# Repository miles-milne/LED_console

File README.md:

WORK IN PROGRESS

Current project of making 2048 using hardware

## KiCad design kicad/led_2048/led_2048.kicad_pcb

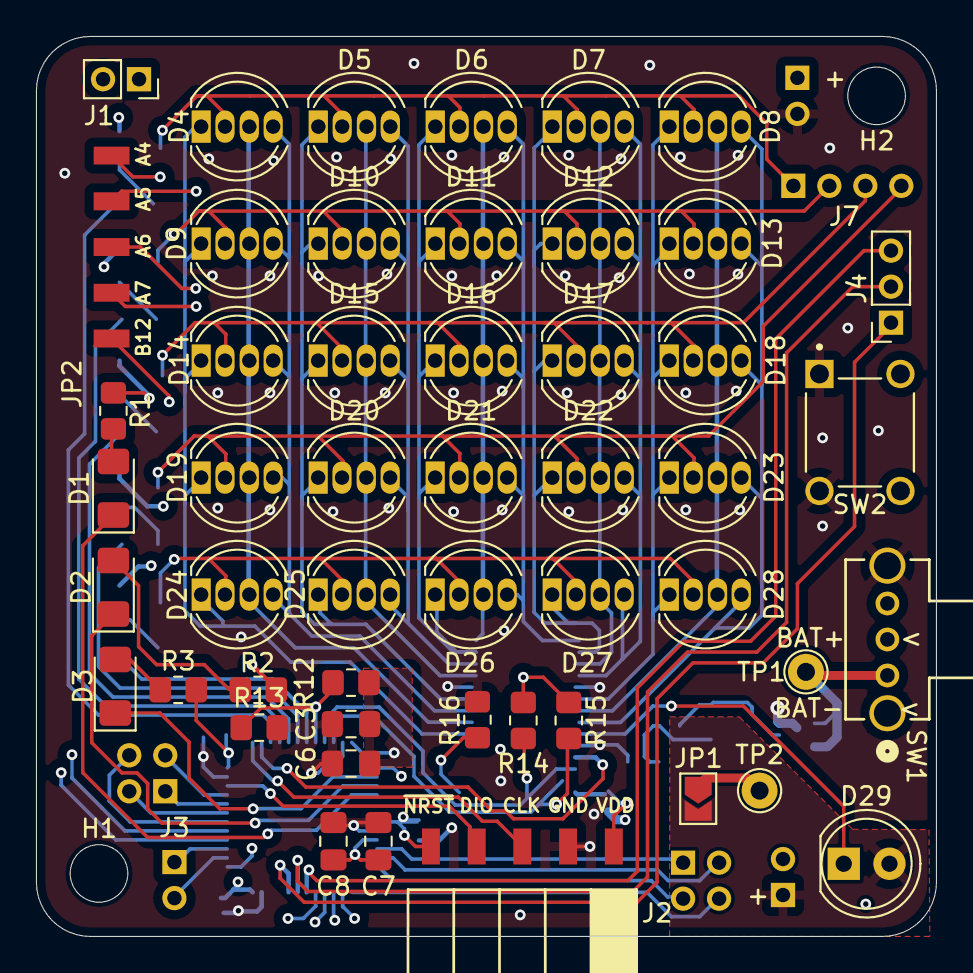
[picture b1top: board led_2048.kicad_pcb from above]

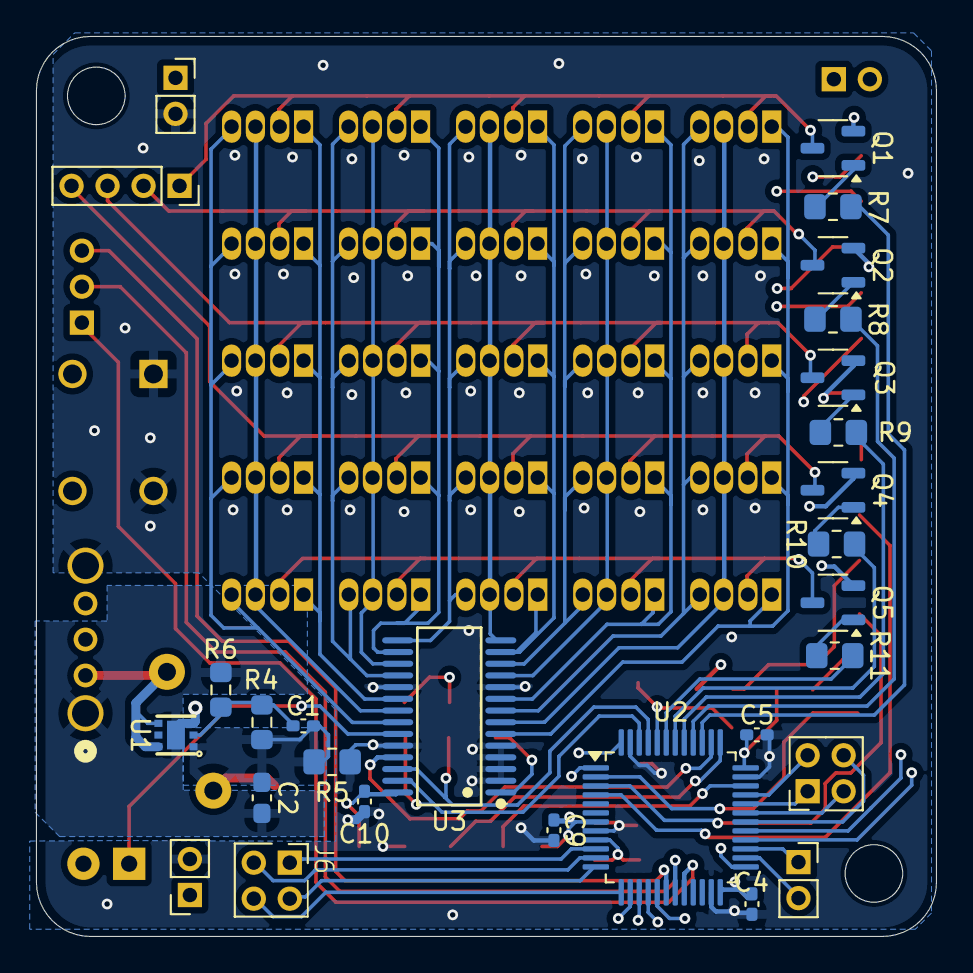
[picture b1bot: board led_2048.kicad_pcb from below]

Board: 6 copper layers, 50.0 x 50.0 mm, 78 parts (26 on the bottom side), 66 nets.

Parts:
C1, C4, C5, C9, C10: 0.1uF; C_0402_1005Metric_Pad0.74x0.62mm_HandSolder
C2: 2.2uF; C_0603_1608Metric_Pad1.08x0.95mm_HandSolder
C3: 4.7uF; C_0805_2012Metric_Pad1.18x1.45mm_HandSolder
C6: 0.1uF; C_0805_2012Metric_Pad1.18x1.45mm_HandSolder
C7: 10nF; C_0805_2012Metric_Pad1.18x1.45mm_HandSolder
C8: 1uF; C_0805_2012Metric_Pad1.18x1.45mm_HandSolder
D1: Blue; LED_1206_3216Metric_Pad1.42x1.75mm_HandSolder
D2: Green; LED_1206_3216Metric_Pad1.42x1.75mm_HandSolder
D3: Red; LED_1206_3216Metric_Pad1.42x1.75mm_HandSolder
D4, D5, D6, D7, D8, D9, D10, D11, D12, D13, D14, D15, D16, D17, D18, D19, D20, D21, D22, D23, D24, D25, D26, D27, D28: RGB; LED_D5.0mm-4x0.8mm_RGB
D29: Green; LED_D5.0mm
H1, H2: MountingHole M3; MountingHole_3.2mm_M3
J1: Misc conn 1; PinSocket_1x02_P2.00mm_Vertical
J2: Program Conn; PinSocket_5x2.54_SMD_90deg_952-3198-1-ND
J3: Misc conn 2; PinSocket_1x02_P2.00mm_Vertical
J4: Shift Reg Conn; PinSocket_1x03_P2.00mm_Vertical
J5, J6: Button conn left; PinSocket_2x02_P2.00mm_Vertical
J7: PinSocket_1x04_P2.00mm_Vertical
JP1: 3.3V; SolderJumper-2_P1.3mm_Open_TrianglePad1.0x1.5mm
JP2: PinSocket_5x2.54_SMD_90deg_952-3198-1-ND
Q1, Q2, Q3, Q4, Q5: PNP; SOT-23-3
R1, R2, R3: 330R; R_0805_2012Metric_Pad1.20x1.40mm_HandSolder
R4: 52.3k; R_0603_1608Metric_Pad0.98x0.95mm_HandSolder
R5: 1k (DNP); R_0805_2012Metric_Pad1.20x1.40mm_HandSolder
R6: 30.1k; R_0603_1608Metric_Pad0.98x0.95mm_HandSolder
R7, R8, R9, R10, R11, R16: 1k; R_0805_2012Metric_Pad1.20x1.40mm_HandSolder
R12: 0R (DNP); R_0805_2012Metric_Pad1.20x1.40mm_HandSolder
R13, R14, R15: 10k; R_0805_2012Metric_Pad1.20x1.40mm_HandSolder
SW1: Power switch; OS102011MA1QN1_CNK
SW2: SW_Push; SW_TL1105SPF160Q
TP1: Battery; TestPoint_THTPad_D2.0mm_Drill1.0mm
TP2: LDO; TestPoint_THTPad_D2.0mm_Drill1.0mm
U1: TPS73701DRVR; WSON-6_L2.0-W2.0-P0.65-BL-EP
U2: STM32F303CBTx; LQFP-48_7x7mm_P0.5mm
U3: TLC59116ITPWRQ1; TSSOP-28_L9.7-W4.4-P0.65-LS6.4-BL

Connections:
/LED Matrix/OUT0: D4.1 (RK), D9.1 (RK), D14.1 (RK), D19.1 (RK), D24.1 (RK), U3.6 (OUT0#)
/LED Matrix/OUT1: D4.3 (GK), D9.3 (GK), D14.3 (GK), D19.3 (GK), D24.3 (GK), U3.7 (OUT1#)
/LED Matrix/OUT2: D4.4 (BK), D9.4 (BK), D14.4 (BK), D19.4 (BK), D24.4 (BK), U3.8 (OUT2#)
/LED Matrix/OUT3: D5.1 (RK), D10.1 (RK), D15.1 (RK), D20.1 (RK), D25.1 (RK), U3.9 (OUT3#)
/LED Matrix/OUT4: D5.3 (GK), D10.3 (GK), D15.3 (GK), D20.3 (GK), D25.3 (GK), U3.11 (OUT4#)
/LED Matrix/OUT5: D5.4 (BK), D10.4 (BK), D15.4 (BK), D20.4 (BK), D25.4 (BK), U3.12 (OUT5#)
/LED Matrix/OUT6: D6.1 (RK), D11.1 (RK), D16.1 (RK), D21.1 (RK), D26.1 (RK), U3.13 (OUT6#)
/LED Matrix/OUT7: D6.3 (GK), D11.3 (GK), D16.3 (GK), D21.3 (GK), D26.3 (GK), U3.14 (OUT7#)
/LED Matrix/OUT8: D6.4 (BK), D11.4 (BK), D16.4 (BK), D21.4 (BK), D26.4 (BK), U3.15 (OUT8#)
/LED Matrix/OUT9: D7.1 (RK), D12.1 (RK), D17.1 (RK), D22.1 (RK), D27.1 (RK), U3.16 (OUT9#)
/LED Matrix/OUT10: D7.3 (GK), D12.3 (GK), D17.3 (GK), D22.3 (GK), D27.3 (GK), U3.17 (OUT10#)
/LED Matrix/OUT11: D7.4 (BK), D12.4 (BK), D17.4 (BK), D22.4 (BK), D27.4 (BK), U3.18 (OUT11#)
/LED Matrix/OUT12: D8.1 (RK), D13.1 (RK), D18.1 (RK), D23.1 (RK), D28.1 (RK), U3.20 (OUT12#)
/LED Matrix/OUT13: D8.3 (GK), D13.3 (GK), D18.3 (GK), D23.3 (GK), D28.3 (GK), U3.21 (OUT13#)
/LED Matrix/OUT14: D8.4 (BK), D13.4 (BK), D18.4 (BK), D23.4 (BK), D28.4 (BK), U3.22 (OUT14#)
/LED Matrix/OUT15: D29.1 (K), U3.23 (OUT15#)
/MCU/Blue LED: D2.1 (K), U2.3 (PC14)
/MCU/Button 1: J5.1, U2.32 (PA11)
/MCU/Button 2: J5.2, U2.31 (PA10)
/MCU/Button 3: J5.3, U2.33 (PA12)
/MCU/Button 4: J5.4, U2.30 (PA9)
/MCU/Button 5: J6.1, U2.10 (PA0)
/MCU/Button 6: J6.2, U2.11 (PA1)
/MCU/Button 7: J6.3, U2.12 (PA2)
/MCU/Button 8: J6.4, U2.13 (PA3)
/MCU/Green LED: D1.1 (K), U2.4 (PC15)
/MCU/MUX1: R7.1, U2.39 (PB3)
/MCU/MUX2: R8.1, U2.40 (PB4)
/MCU/MUX3: R9.1, U2.41 (PB5)
/MCU/MUX4: R10.1, U2.42 (PB6)
/MCU/MUX5: R11.1, U2.43 (PB7)
/MCU/Misc GPIO 1: J1.1, U2.29 (PA8)
/MCU/Misc GPIO 2: J1.2, U2.28 (PB15)
/MCU/Misc GPIO 3: J3.1, U2.27 (PB14)
/MCU/Misc GPIO 4: J3.2, U2.26 (PB13)
/MCU/Red LED: D3.1 (K), U2.2 (PC13)
/MCU/SWCLK: J2.3, U2.37 (PA14)
/MCU/SWDIO: J2.4, U2.34 (PA13)
/MCU/Score clk: J4.3, U2.18 (PB0)
/MCU/Score data: J4.1, U2.20 (PB2)
/MCU/Score latch: J4.2, U2.19 (PB1)
/MCU/~BOOT: R12.2, R13.1, U2.44 (BOOT0)
/MCU/~RESET: C9.1, J2.5, SW2.3 (K), SW2.4 (A), U2.7 (NRST)
GND: C2.2, C3.2, C4.2, C5.2, C6.2, C7.2, C8.2, C9.2, C10.1, J2.2, R5.1, R6.1, R13.2, R16.1, SW1.4 (SH1), SW1.5 (SH2), SW2.1, SW2.2, U1.3 (GND), U1.7 (EP), U2.8 (VSSA), U2.23 (VSS), U2.35 (VSS), U2.47 (VSS), U3.2 (A0), U3.3 (A1), U3.4 (A2), U3.5 (A3), U3.10 (GND), U3.19 (GND), U3.24 (GND)
Multiplex 1: D4.2 (A), D5.2 (A), D6.2 (A), D7.2 (A), D8.2 (A), J7.1, Q1.3 (C)
Multiplex 2: D9.2 (A), D10.2 (A), D11.2 (A), D12.2 (A), D13.2 (A), J7.2, Q2.3 (C)
Multiplex 3: D14.2 (A), D15.2 (A), D16.2 (A), D17.2 (A), D18.2 (A), J7.3, Q3.3 (C)
Multiplex 4: D19.2 (A), D20.2 (A), D21.2 (A), D22.2 (A), D23.2 (A), J7.4, Q4.3 (C)
Multiplex 5: D24.2 (A), D25.2 (A), D26.2 (A), D27.2 (A), D28.2 (A), Q5.3 (C)
unnamed: D1.2 (A), R1.2
unnamed: D2.2 (A), R2.2
unnamed: D3.2 (A), R3.2
unnamed: C1.1, C2.1, JP1.1 (A), R4.2, R5.2, TP2.1, U1.1 (OUT)
unnamed: Q1.1 (B), R7.2
unnamed: Q2.1 (B), R8.2
unnamed: Q3.1 (B), R9.2
unnamed: Q4.1 (B), R10.2
unnamed: Q5.1 (B), R11.2
unnamed: SW1.1 (A), TP1.1, U1.4 (EN), U1.6 (IN)
unnamed: C1.2, R4.1, R6.2, U1.2 (NR/FB)
unnamed: C7.1, C8.1, U2.9 (VDDA)
unnamed: R16.2, U3.1 (REXT)
SCL: R14.2, U2.45 (PB8), U3.26 (SCL)
SDA: R15.2, U2.46 (PB9), U3.27 (SDA)
TLC Reset: U2.38 (PA15), U3.25 (RESET#)
VDD: C3.1, C4.1, C5.1, C6.1, C10.2, D29.2 (A), J2.1, JP1.2 (B), Q1.2 (E), Q2.2 (E), Q3.2 (E), Q4.2 (E), Q5.2 (E), R1.1, R2.1, R3.1, R12.1, R14.1, R15.1, U2.1 (VBAT), U2.24 (VDD), U2.36 (VDD), U2.48 (VDD), U3.28 (VCC)

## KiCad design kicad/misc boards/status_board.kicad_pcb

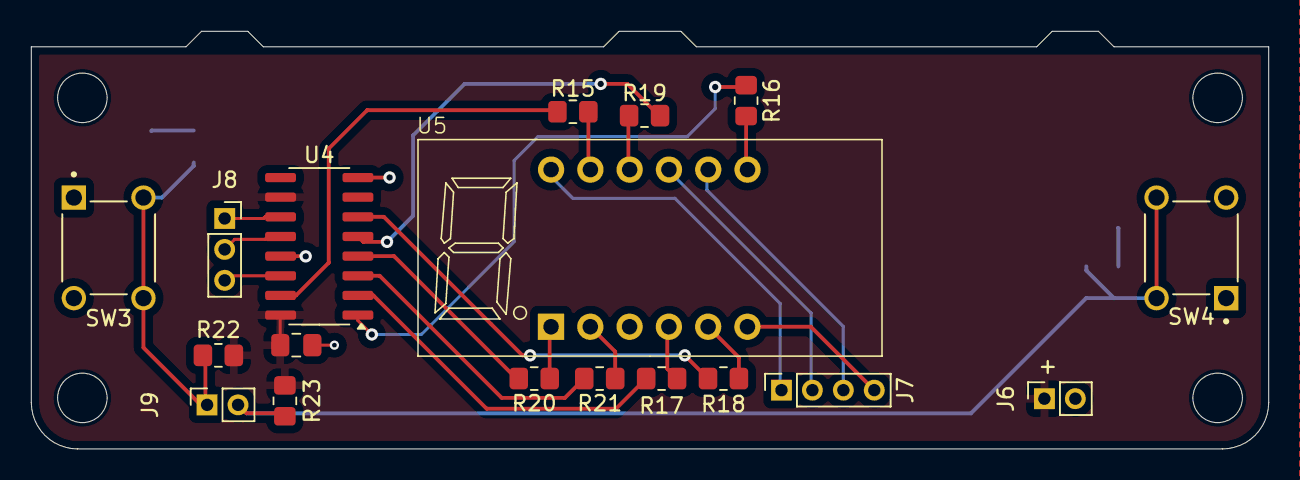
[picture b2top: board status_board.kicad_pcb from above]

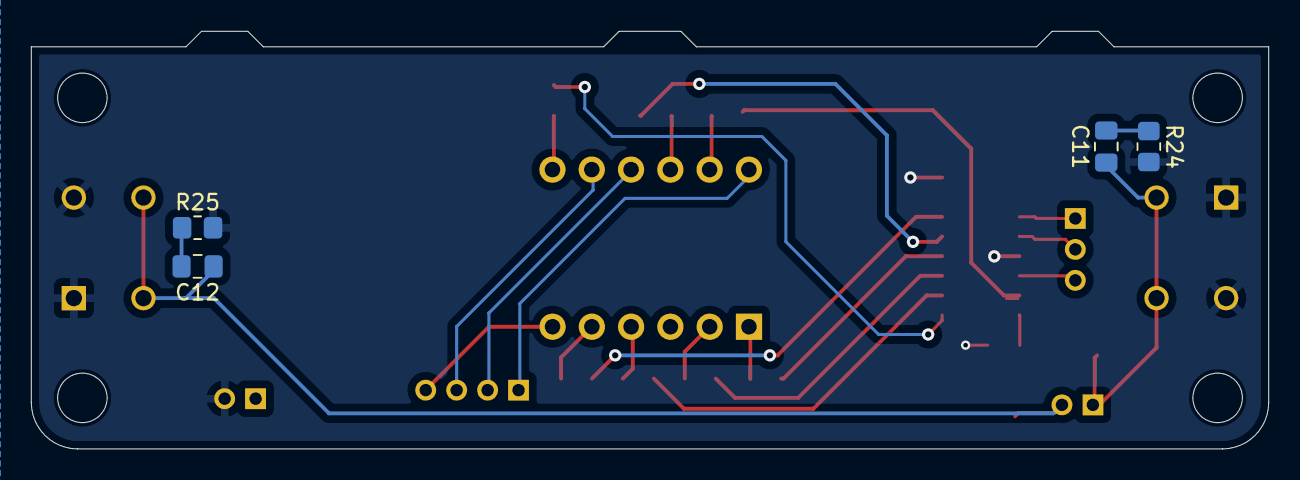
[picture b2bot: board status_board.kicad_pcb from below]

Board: 2 copper layers, 80.0 x 27.0 mm, 21 parts (4 on the bottom side), 27 nets.

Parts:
C11, C12: 0.1uF (DNP); C_0805_2012Metric_Pad1.18x1.45mm_HandSolder
J6: Power conn; PinSocket_1x02_P2.00mm_Vertical
J7: Mux Conn; PinSocket_1x04_P2.00mm_Vertical
J8: Shift Reg Conn; PinSocket_1x03_P2.00mm_Vertical
J9: Misc conn 1; PinSocket_1x02_P2.00mm_Vertical
R15, R16, R17, R18, R19, R20, R21: 220R; R_0805_2012Metric_Pad1.20x1.40mm_HandSolder
R22, R23: 4.7k; R_0805_2012Metric_Pad1.20x1.40mm_HandSolder
R24, R25: 100R (DNP); R_0805_2012Metric_Pad1.20x1.40mm_HandSolder
SW3, SW4: Button; SW_TL1105SPF160Q
U4: 74HC595; SOP-16_3.9x9.9mm_P1.27mm
U5: CL3641BH

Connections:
/Score display/A: R15.2, U5.11 (a)
/Score display/B: R16.2, U5.7 (b)
/Score display/Button 9: C11.1, J9.1, R22.1, SW3.3 (K), SW3.4 (A)
/Score display/Button 10: C12.1, J9.2, R23.1, SW4.3 (K), SW4.4 (A)
/Score display/C: R17.2, U5.4 (c)
/Score display/D: R21.1, U5.2 (d)
/Score display/E: R20.1, U5.1 (e)
/Score display/F: R19.1, U5.10 (f)
/Score display/G: R18.1, U5.5 (g)
GND: J6.2, R24.2, R25.2, SW3.1, SW3.2, SW4.1, SW4.2, U4.8 (GND), U4.13 (~OE)
Multiplex 1: J7.1, U5.12 (CA1)
Multiplex 2: J7.2, U5.9 (CA2)
Multiplex 3: J7.3, U5.8 (CA3)
Multiplex 4: J7.4, U5.6 (CA4)
unnamed: C11.2, R24.1
unnamed: C12.2, R25.1
unnamed: R15.1, U4.15 (QA)
unnamed: R16.1, U4.1 (QB)
unnamed: R17.1, U4.2 (QC)
unnamed: R21.2, U4.3 (QD)
unnamed: R20.2, U4.4 (QE)
unnamed: R19.2, U4.5 (QF)
unnamed: R18.2, U4.6 (QG)
Score clk: J8.1, U4.11 (SRCLK)
Score data: J8.3, U4.14 (SER)
Score latch: J8.2, U4.12 (RCLK)
VDD: J6.1, R22.2, R23.2, U4.10 (~SRCLR), U4.16 (VCC)

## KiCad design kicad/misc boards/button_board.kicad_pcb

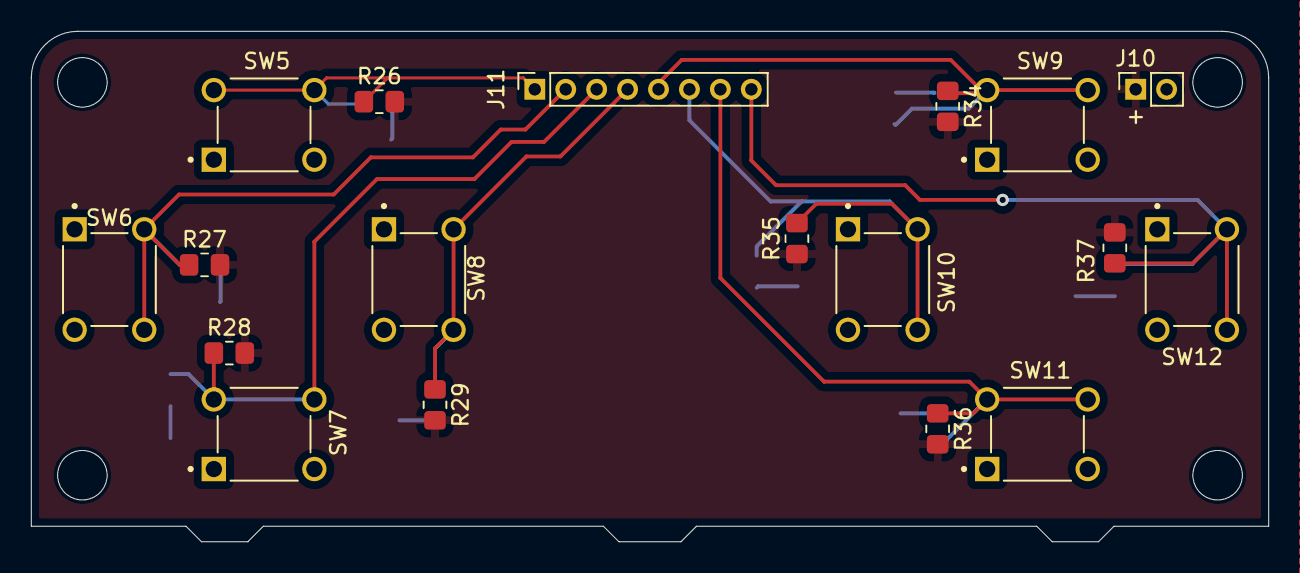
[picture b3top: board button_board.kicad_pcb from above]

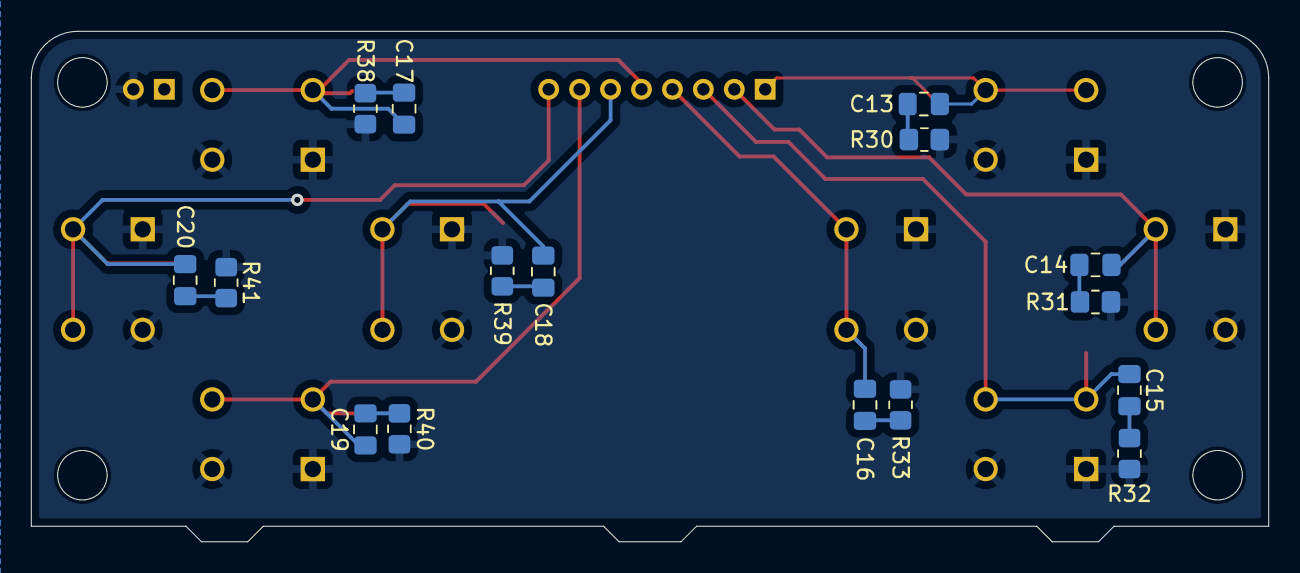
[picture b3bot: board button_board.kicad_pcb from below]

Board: 2 copper layers, 80.0 x 33.0 mm, 34 parts (16 on the bottom side), 18 nets.

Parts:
C13, C14, C15, C16, C17, C18, C19, C20: 0.1uF (DNP); C_0805_2012Metric_Pad1.18x1.45mm_HandSolder
J10: Power conn; PinSocket_1x02_P2.00mm_Vertical
J11: Button conn; PinSocket_1x08_P2.00mm_Vertical
R26, R27, R28, R29, R34, R35, R36, R37: 4.7k; R_0805_2012Metric_Pad1.20x1.40mm_HandSolder
R30, R31, R32, R33, R38, R39, R40, R41: 100R (DNP); R_0805_2012Metric_Pad1.20x1.40mm_HandSolder
SW5, SW6, SW7, SW8, SW9, SW10, SW11, SW12: Button; SW_TL1105SPF160Q

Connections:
/Press buttons/Button 1: C13.1, J11.1, R26.1, SW5.3 (K), SW5.4 (A)
/Press buttons/Button 2: C14.1, J11.2, R27.1, SW6.3 (K), SW6.4 (A)
/Press buttons/Button 3: C15.1, J11.3, R28.1, SW7.3 (K), SW7.4 (A)
/Press buttons/Button 4: C16.1, J11.4, R29.1, SW8.3 (K), SW8.4 (A)
/Press buttons/Button 5: C17.1, J11.5, R34.1, SW9.3 (K), SW9.4 (A)
/Press buttons/Button 6: C18.1, J11.6, R35.1, SW10.3 (K), SW10.4 (A)
/Press buttons/Button 7: C19.1, J11.7, R36.1, SW11.3 (K), SW11.4 (A)
/Press buttons/Button 8: C20.1, J11.8, R37.1, SW12.3 (K), SW12.4 (A)
GND: J10.2, R30.2, R31.2, R32.2, R33.2, R38.2, R39.2, R40.2, R41.2, SW5.1, SW5.2, SW6.1, SW6.2, SW7.1, SW7.2, SW8.1, SW8.2, SW9.1, SW9.2, SW10.1, SW10.2, SW11.1, SW11.2, SW12.1, SW12.2
unnamed: C13.2, R30.1
unnamed: C14.2, R31.1
unnamed: C15.2, R32.1
unnamed: C16.2, R33.1
unnamed: C17.2, R38.1
unnamed: C18.2, R39.1
unnamed: C19.2, R40.1
unnamed: C20.2, R41.1
VDD: J10.1, R26.2, R27.2, R28.2, R29.2, R34.2, R35.2, R36.2, R37.2

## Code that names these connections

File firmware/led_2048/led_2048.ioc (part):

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Mcu.Name=STM32F303C(B-C)Tx
Mcu.Package=LQFP48
Mcu.UserName=STM32F303CBTx
PA0.Signal=GPIO_Input
PA1.Signal=GPIO_Input
PA10.Signal=GPIO_Input
PA11.Signal=GPIO_Input
PA12.Signal=GPIO_Input
PA13.Signal=SYS_JTMS-SWDIO
PA14.Signal=SYS_JTCK-SWCLK
PA15.Signal=GPIO_Output
PA2.Signal=GPIO_Input
PA3.Signal=GPIO_Input
PA4.Signal=GPIO_Output
PA5.Signal=GPIO_Output
PA8.Signal=GPIO_Input
PA9.Signal=GPIO_Input
PB15.Signal=GPIO_Input
PB3.Signal=GPIO_Output
PB4.Signal=GPIO_Output
PB5.Signal=GPIO_Output
PB6.Signal=GPIO_Output
PB7.Signal=GPIO_Output
PB8.GPIOParameters=GPIO_Speed,GPIO_FM8,GPIO_Pu,GPIO_Mode
PB8.GPIO_FM8=__NULL
PB8.GPIO_Mode=GPIO_MODE_AF_OD
PB8.GPIO_Pu=GPIO_NOPULL
PB8.GPIO_Speed=GPIO_SPEED_FREQ_HIGH
PB8.Mode=I2C
PB8.Signal=I2C1_SCL
PB9.GPIOParameters=GPIO_Speed,GPIO_Pu,GPIO_Mode,GPIO_FM9
PB9.GPIO_FM9=__NULL
PB9.GPIO_Mode=GPIO_MODE_AF_OD
PB9.GPIO_Pu=GPIO_NOPULL
PB9.GPIO_Speed=GPIO_SPEED_FREQ_HIGH
PB9.Mode=I2C
PB9.Signal=I2C1_SDA
PC13.Signal=GPIO_Output
RCC.HSEPLLFreq_Value=8000000
RCC.HSE_VALUE=8000000
RCC.SYSCLKFreq_VALUE=8000000
board=custom

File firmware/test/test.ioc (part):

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Mcu.Name=STM32F401R(D-E)Tx
Mcu.Package=LQFP64
Mcu.UserName=STM32F401RETx
PA13.GPIOParameters=GPIO_Label
PA13.GPIO_Label=TMS
PA13.Mode=Serial_Wire
PA13.Signal=SYS_JTMS-SWDIO
PA14.GPIOParameters=GPIO_Label
PA14.GPIO_Label=TCK
PA14.Mode=Serial_Wire
PA14.Signal=SYS_JTCK-SWCLK
PA2.GPIOParameters=GPIO_Speed,GPIO_PuPd,GPIO_Label,GPIO_Mode
PA2.GPIO_Label=USART_TX
PA2.GPIO_Mode=GPIO_MODE_AF_PP
PA2.GPIO_PuPd=GPIO_NOPULL
PA2.GPIO_Speed=GPIO_SPEED_FREQ_LOW
PA2.Mode=Asynchronous
PA2.Signal=USART2_TX
PA3.GPIOParameters=GPIO_Speed,GPIO_PuPd,GPIO_Label,GPIO_Mode
PA3.GPIO_Label=USART_RX
PA3.GPIO_Mode=GPIO_MODE_AF_PP
PA3.GPIO_PuPd=GPIO_NOPULL
PA3.GPIO_Speed=GPIO_SPEED_FREQ_LOW
PA3.Mode=Asynchronous
PA3.Signal=USART2_RX
PA5.GPIOParameters=GPIO_Speed,GPIO_PuPd,GPIO_Label,GPIO_Mode
PA5.GPIO_Label=LD2 [Green Led]
PA5.GPIO_Mode=GPIO_MODE_OUTPUT_PP
PA5.GPIO_PuPd=GPIO_NOPULL
PA5.GPIO_Speed=GPIO_SPEED_FREQ_LOW
PA5.Signal=GPIO_Output
PB1.Signal=GPIO_Output
PB13.Signal=GPIO_Output
PB14.Signal=GPIO_Output
PB15.Signal=GPIO_Output
PB3.GPIOParameters=GPIO_Label
PB3.GPIO_Label=SWO
PB3.Signal=SYS_JTDO-SWO
PC0.Signal=GPIO_Output
PC1.Signal=GPIO_Output
PC13-ANTI_TAMP.GPIOParameters=GPIO_PuPd,GPIO_Label,GPIO_ModeDefaultEXTI
PC13-ANTI_TAMP.GPIO_Label=B1 [Blue PushButton]
PC13-ANTI_TAMP.GPIO_ModeDefaultEXTI=GPIO_MODE_IT_FALLING
PC13-ANTI_TAMP.GPIO_PuPd=GPIO_NOPULL
PC13-ANTI_TAMP.Signal=GPXTI13
PC14-OSC32_IN.Mode=LSE-External-Oscillator
PC14-OSC32_IN.Signal=RCC_OSC32_IN
PC15-OSC32_OUT.Mode=LSE-External-Oscillator
PC15-OSC32_OUT.Signal=RCC_OSC32_OUT
PC2.Signal=GPIO_Output
PC5.Signal=GPIO_Input
PH0\ -\ OSC_IN.Mode=HSE-External-Clock-Source
PH0\ -\ OSC_IN.Signal=RCC_OSC_IN
PH1\ -\ OSC_OUT.Mode=HSE-External-Clock-Source
PH1\ -\ OSC_OUT.Signal=RCC_OSC_OUT
RCC.HSE_VALUE=8000000
RCC.SYSCLKFreq_VALUE=84000000
RCC.SYSCLKSource=RCC_SYSCLKSOURCE_PLLCLK
board=NUCLEO-F401RE
boardIOC=true

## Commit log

2024-07-03 init commit
2024-07-04 first software 2048 prototype
2024-07-04 finished code prototype
2024-07-04 minor code revisions
2024-07-29 minor revisions
2024-08-01 finished layout
2024-08-15 finalized boards and cad files
2024-09-09 major revisions
2024-09-15 updated .gitignore for firmware log files
2024-09-15 more work on button and display drivers
2024-09-16 functional prototype completed
2024-09-16 renamed project
2024-09-17 added solderbridge for bootloader
2024-10-11 revised chassis
2024-10-11 minor schematic revisions
